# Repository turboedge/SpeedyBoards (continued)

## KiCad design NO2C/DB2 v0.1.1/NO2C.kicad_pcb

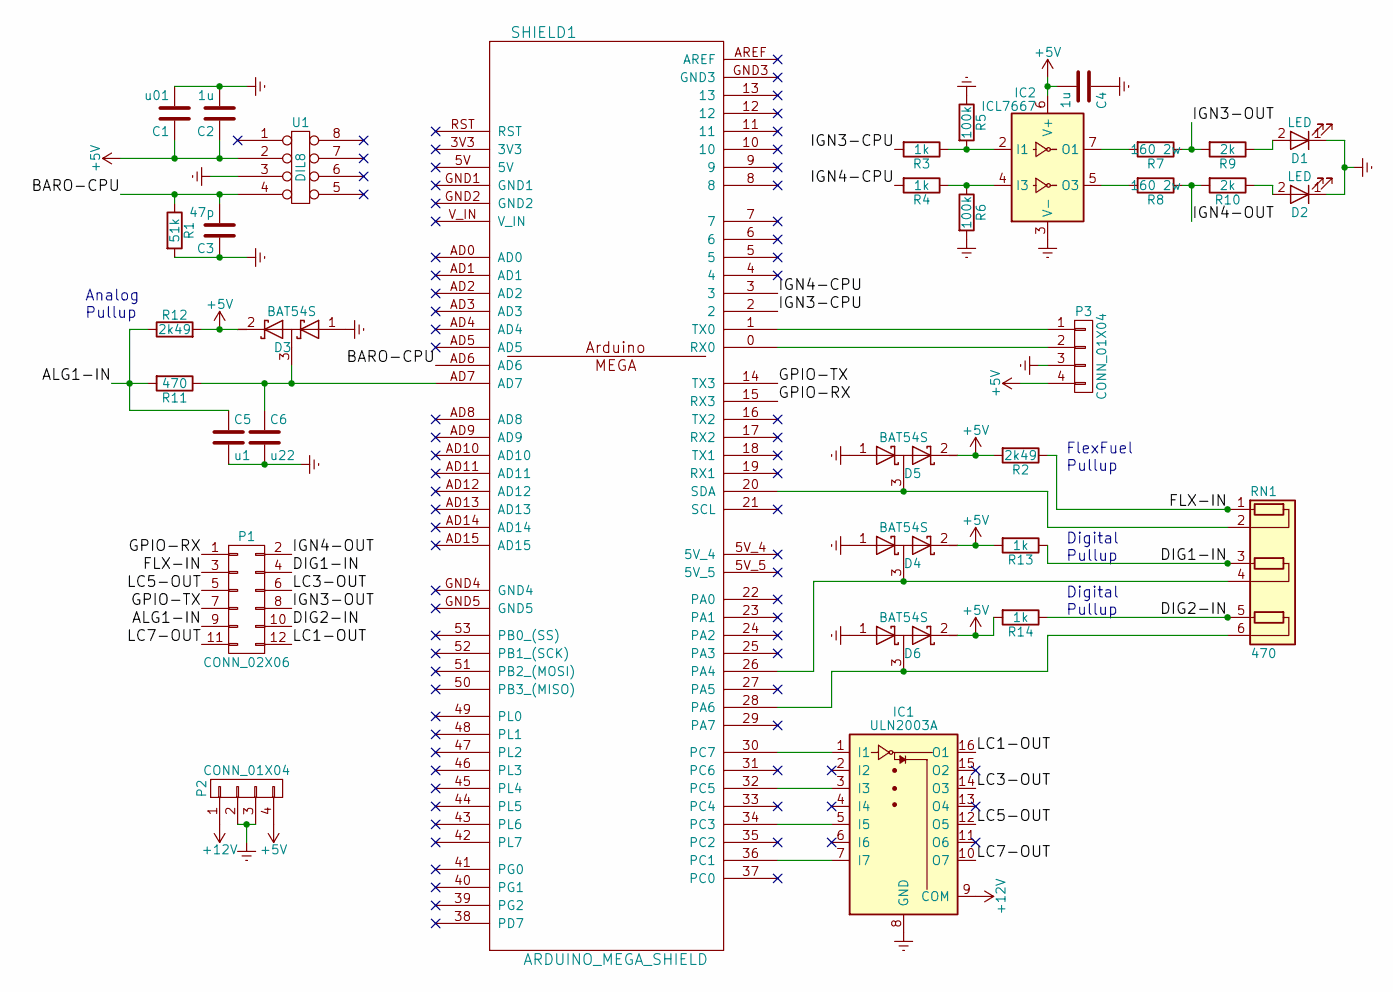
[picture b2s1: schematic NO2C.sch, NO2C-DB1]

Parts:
C1: u01; C_Disc_D3.8mm_W2.6mm_P2.50mm
C2, C4: 1u; C_Disc_D5.1mm_W3.2mm_P5.00mm
C3: 47p; C_1206_HandSoldering
C5: u1; C_Disc_D3.8mm_W2.6mm_P2.50mm
C6: u22; C_Disc_D3.8mm_W2.6mm_P2.50mm
D1, D2: LED; LED_D3.0mm
D3, D4, D5, D6: BAT54S; SOT-23_Handsoldering
IC1: ULN2003A; SOIC-16_3.9x9.9mm_Pitch1.27mm
IC2: ICL7667; DIP-8_W7.62mm
P1: CONN_02X06; Molex_Microfit3_Header_02x06_Straight_43045-1228
P2, P3: CONN_01X04; Pin_Header_Straight_1x04_Pitch2.54mm
R1: 51k; R_1206_HandSoldering
R2, R12: 2k49; R_Axial_DIN0207_L6.3mm_D2.5mm_P7.62mm_Horizontal
R3, R4: 1k; R_Axial_DIN0207_L6.3mm_D2.5mm_P7.62mm_Horizontal
R5, R6: 100k; R_Axial_DIN0204_L3.6mm_D1.6mm_P7.62mm_Horizontal
R7, R8: 160 2w; R_Axial_DIN0411_L9.9mm_D3.6mm_P12.70mm_Horizontal
R9, R10: 2k; R_Axial_DIN0207_L6.3mm_D2.5mm_P7.62mm_Horizontal
R11: 470; R_Axial_DIN0207_L6.3mm_D2.5mm_P7.62mm_Horizontal
R13, R14: 1k; R_1206
RN1: 470; R_Array_SIP6
SHIELD1: ARDUINO_MEGA_SHIELD; ARDUINO_MEGA_SHIELD_DB
U1: DIL8; SSO-8_9.6x6.3mm_Pitch1.27mm_Clearance10.5mm

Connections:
+5V: C1.1, C2.1, C4.2, D3.2 (K), D4.2 (K), D5.2 (K), D6.2 (K), IC2.6 (V+), P2.4, P3.4, R2.2, R12.2, R13.2, R14.2, U1.2
+12V: IC1.9 (COM), P2.1
/ALG1-IN: C5.1, P1.9, R11.2, R12.1
/BARO-CPU: C3.2, R1.1, SHIELD1.AD6, U1.4
/DIG1-IN: P1.4, R13.1, RN1.3 (R2.1)
/DIG2-IN: P1.10, R14.1, RN1.5 (R3.1)
/FLX-IN: P1.3, R2.1, RN1.1 (R1.1)
/GPIO-RX: P1.1, SHIELD1.15 (RX3)
/GPIO-TX: P1.7, SHIELD1.14 (TX3)
/IGN3-CPU: R3.2, SHIELD1.2
/IGN3-OUT: P1.8, R7.1, R9.2
/IGN4-CPU: R4.2, SHIELD1.3
/IGN4-OUT: P1.2, R8.1, R10.2
/LC1-OUT: IC1.16 (O1), P1.12
/LC3-OUT: IC1.14 (O3), P1.6
/LC5-OUT: IC1.12 (O5), P1.5
/LC7-OUT: IC1.10 (O7), P1.11
Earth: C1.2, C2.2, C3.1, C4.1, C5.2, C6.2, D1.1 (K), D2.1 (K), D3.1 (A), D4.1 (A), D5.1 (A), D6.1 (A), IC1.8 (GND), IC2.3 (V-), P2.2, P2.3, P3.3, R1.2, R5.1, R6.2, U1.3
unnamed: C6.1, D3.3 (common), R11.1, SHIELD1.AD7
unnamed: D1.2 (A), R9.1
unnamed: D2.2 (A), R10.1
unnamed: D4.3 (common), RN1.4 (R2.2), SHIELD1.26 (PA4)
unnamed: D5.3 (common), RN1.2 (R1.2), SHIELD1.20 (SDA)
unnamed: D6.3 (common), RN1.6 (R3.2), SHIELD1.28 (PA6)
unnamed: IC1.1 (I1), SHIELD1.30 (PC7)
unnamed: IC1.3 (I3), SHIELD1.32 (PC5)
unnamed: IC1.5 (I5), SHIELD1.34 (PC3)
unnamed: IC1.7 (I7), SHIELD1.36 (PC1)
unnamed: IC2.2 (I1), R3.1, R5.2
unnamed: IC2.4 (I3), R4.1, R6.1
unnamed: IC2.5 (O3), R8.2
unnamed: IC2.7 (O1), R7.2
unnamed: P3.1, SHIELD1.1 (TX0)
unnamed: P3.2, SHIELD1.0 (RX0)

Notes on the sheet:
FlexFuel Pullup
Digital Pullup
Analog Pullup

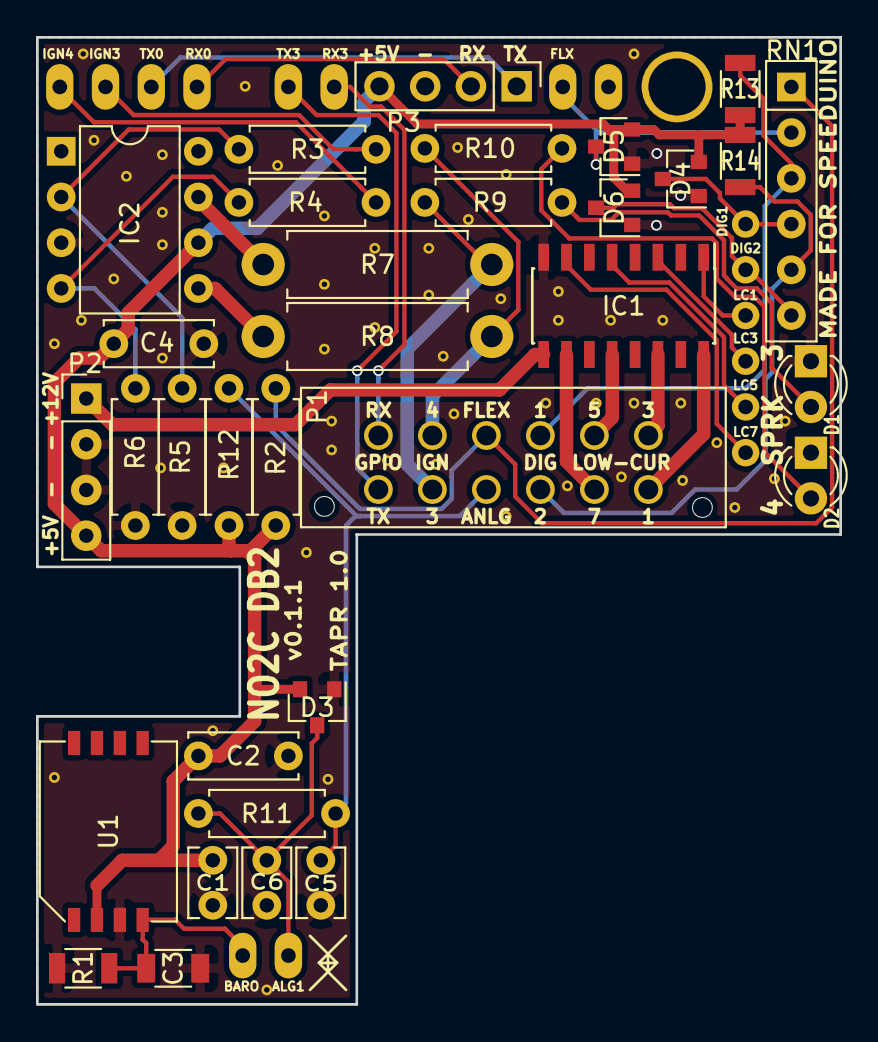
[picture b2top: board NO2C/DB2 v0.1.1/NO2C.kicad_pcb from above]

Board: 2 copper layers, 44.6 x 53.7 mm, 34 parts (0 on the bottom side), 34 nets.

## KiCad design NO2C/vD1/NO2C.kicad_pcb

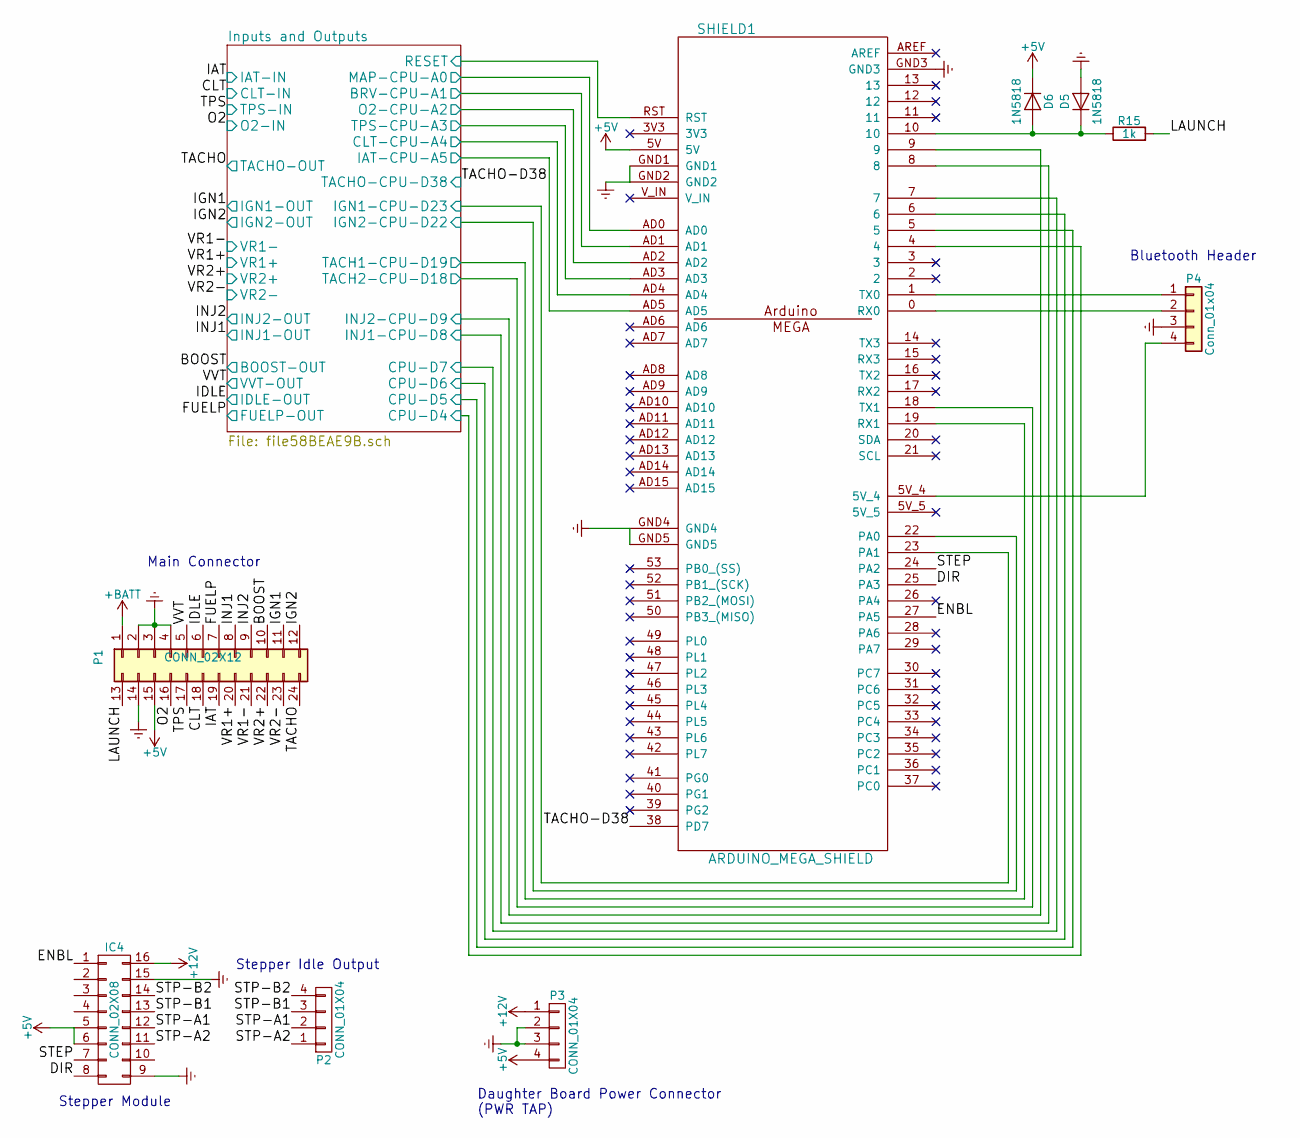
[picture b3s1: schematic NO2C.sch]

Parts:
D5, D6: 1N5818; D_DO-41_SOD81_P7.62mm_Horizontal
IC4: CONN_02X08; DRV8825
P1: CONN_02X12; Molex_Microfit3_Header_02x12_Straight_43045-2428
P2: CONN_01X04; Molex_Microfit3_Header_02x02_Angled_43045-040x
P3: CONN_01X04; Pin_Header_Straight_1x04_Pitch2.54mm
P4: Conn_01x04; Socket_Strip_Straight_1x04_Pitch2.54mm
R15: 1k; R_Axial_DIN0207_L6.3mm_D2.5mm_P7.62mm_Horizontal
SHIELD1: ARDUINO_MEGA_SHIELD

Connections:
+5V: D6.1 (K), IC4.5, IC4.6, P1.15, P3.4, SHIELD1.5V; also elsewhere on the board
+12V: IC4.16, P1.1, P3.1; also elsewhere on the board
/BOOST: P1.10; also elsewhere on the board
/CLT: P1.18; also elsewhere on the board
/DIR: IC4.8, SHIELD1.25 (PA3)
/ENBL: IC4.1, SHIELD1.27 (PA5)
/FUELP: P1.7; also elsewhere on the board
/IAT: P1.19; also elsewhere on the board
/IDLE: P1.6; also elsewhere on the board
/IGN1: P1.11; also elsewhere on the board
/IGN2: P1.12; also elsewhere on the board
/INJ1: P1.8; also elsewhere on the board
/INJ2: P1.9; also elsewhere on the board
/Inputs and Outputs/BRV-CPU-A1: SHIELD1.AD1; also elsewhere on the board
/Inputs and Outputs/CLT-CPU-A4: SHIELD1.AD4; also elsewhere on the board
/Inputs and Outputs/CPU-D4: SHIELD1.4; also elsewhere on the board
/Inputs and Outputs/CPU-D5: SHIELD1.5; also elsewhere on the board
/Inputs and Outputs/CPU-D6: SHIELD1.6; also elsewhere on the board
/Inputs and Outputs/CPU-D7: SHIELD1.7; also elsewhere on the board
/Inputs and Outputs/IAT-CPU-A5: SHIELD1.AD5; also elsewhere on the board
/Inputs and Outputs/IGN1-CPU-D23: SHIELD1.23 (PA1); also elsewhere on the board
/Inputs and Outputs/IGN2-CPU-D22: SHIELD1.22 (PA0); also elsewhere on the board
/Inputs and Outputs/INJ1-CPU-D8: SHIELD1.8; also elsewhere on the board
/Inputs and Outputs/INJ2-CPU-D9: SHIELD1.9; also elsewhere on the board
/Inputs and Outputs/MAP-CPU-A0: SHIELD1.AD0; also elsewhere on the board
/Inputs and Outputs/O2-CPU-A2: SHIELD1.AD2; also elsewhere on the board
/Inputs and Outputs/RESET: SHIELD1.RST; also elsewhere on the board
/Inputs and Outputs/TACH1-CPU-D19: SHIELD1.19 (RX1); also elsewhere on the board
/Inputs and Outputs/TACH2-CPU-D18: SHIELD1.18 (TX1); also elsewhere on the board
/Inputs and Outputs/TPS-CPU-A3: SHIELD1.AD3; also elsewhere on the board
/LAUNCH: P1.13, R15.2
/O2: P1.16; also elsewhere on the board
/STEP: IC4.7, SHIELD1.24 (PA2)
/STP-A1: IC4.12, P2.2
/STP-A2: IC4.11, P2.1
/STP-B1: IC4.13, P2.3
/STP-B2: IC4.14, P2.4
/TACHO: P1.24; also elsewhere on the board
/TACHO-D38: SHIELD1.38 (PD7); also elsewhere on the board
/TPS: P1.17; also elsewhere on the board
/VR1+: P1.20; also elsewhere on the board
/VR1-: P1.21; also elsewhere on the board
/VR2+: P1.22; also elsewhere on the board
/VR2-: P1.23; also elsewhere on the board
/VVT: P1.5; also elsewhere on the board
Earth: D5.2 (A), IC4.9, IC4.15, P1.2, P1.3, P1.4, P1.14, P3.2, P3.3, P4.3, SHIELD1.GND1, SHIELD1.GND2, SHIELD1.GND3, SHIELD1.GND4, SHIELD1.GND5; also elsewhere on the board
unnamed: D5.1 (K), D6.2 (A), R15.1, SHIELD1.10
unnamed: P4.1, SHIELD1.1 (TX0)
unnamed: P4.2, SHIELD1.0 (RX0)
unnamed: P4.4, SHIELD1.5V_4

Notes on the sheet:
Stepper Module
Daughter Board Power Connector (PWR TAP)
Bluetooth Header
Stepper Idle Output
Main Connector

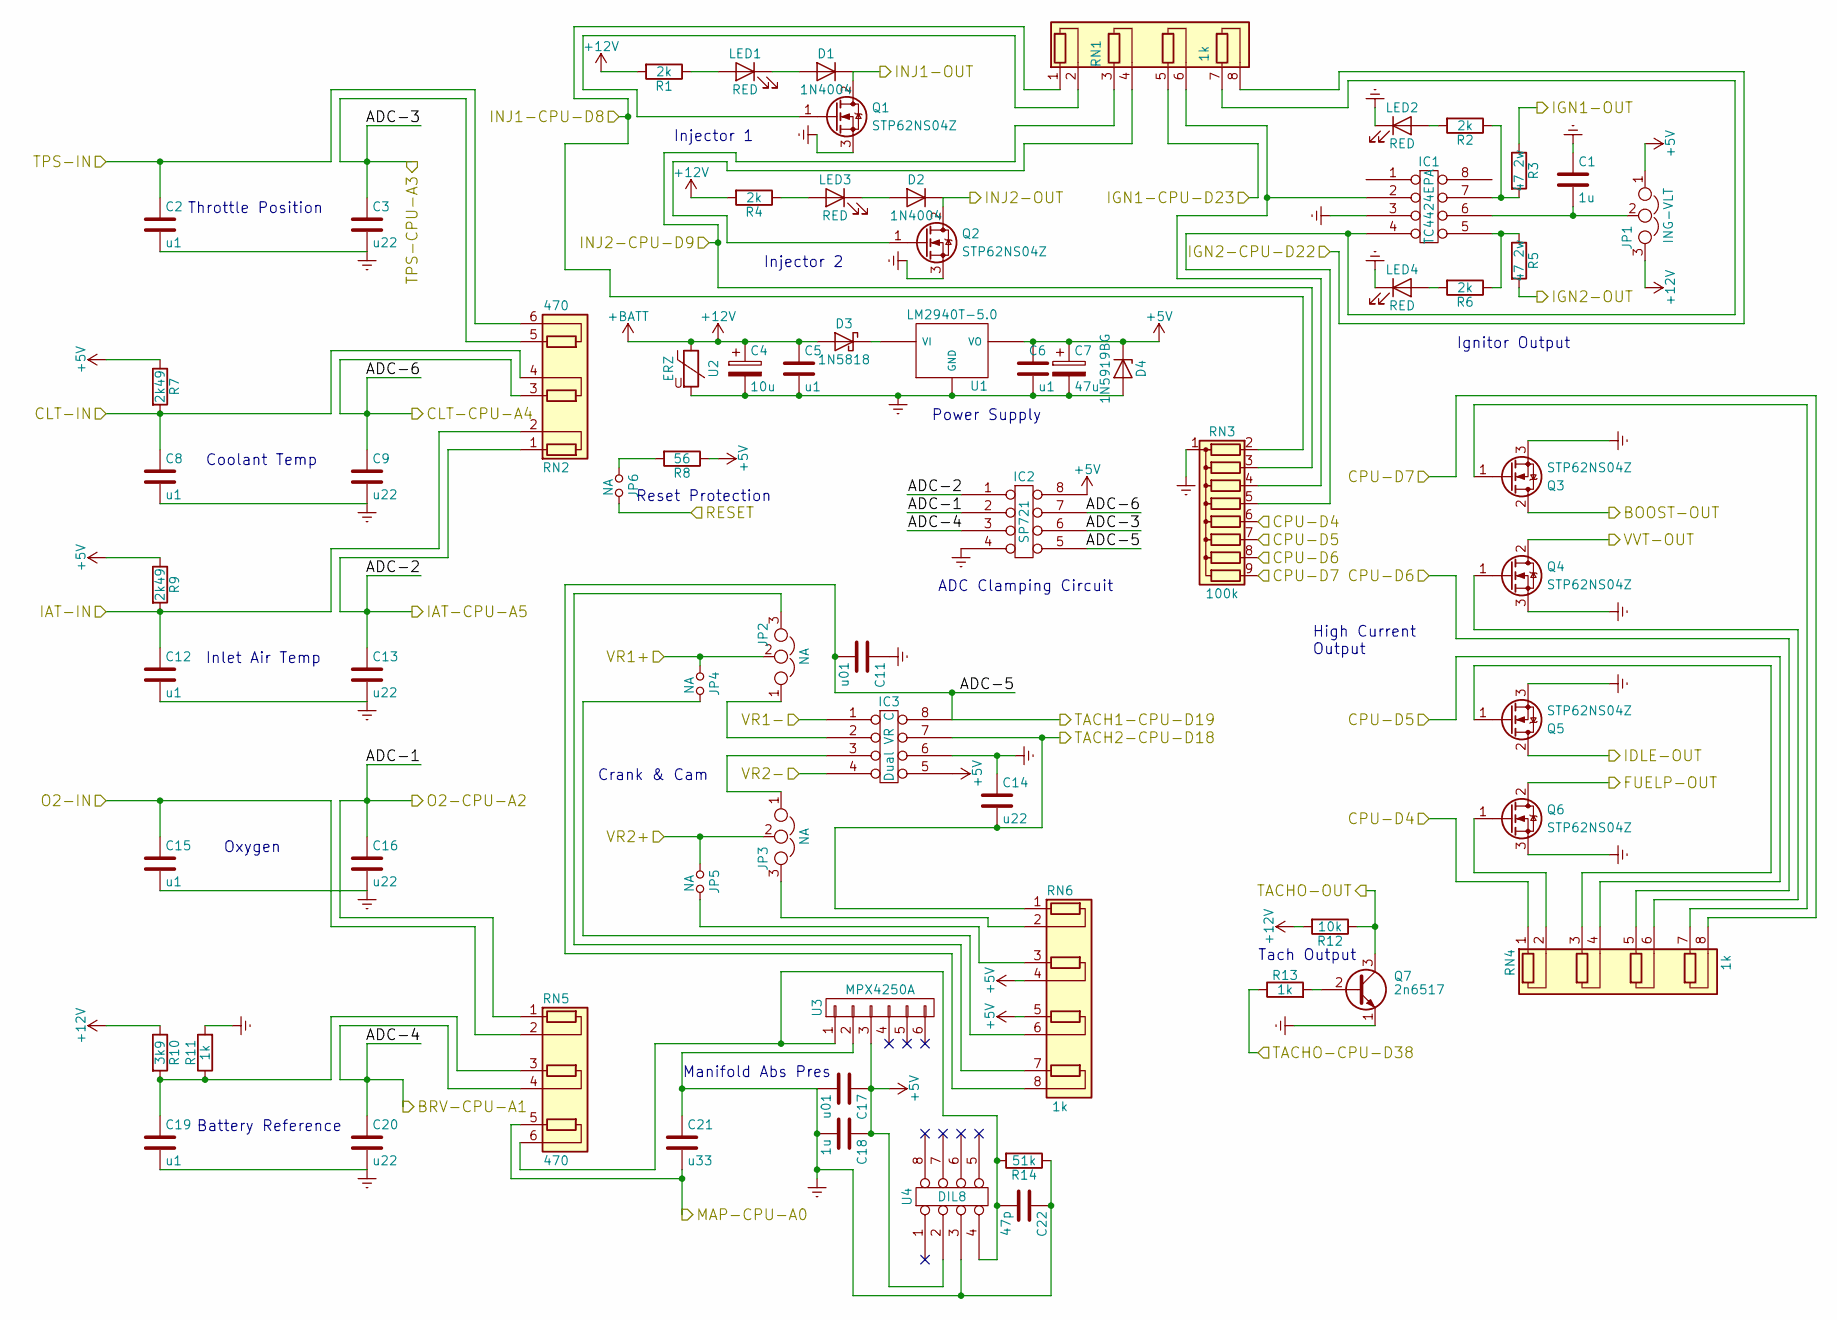
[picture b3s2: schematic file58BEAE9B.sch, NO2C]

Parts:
C1, C18: 1u; C_Disc_D6.0mm_W2.5mm_P5.00mm
C2, C5, C6, C8, C12, C15, C19: u1; C_Disc_D3.8mm_W2.6mm_P2.50mm
C3, C9, C13, C14, C16, C20: u22; C_Disc_D3.8mm_W2.6mm_P2.50mm
C4: 10u; CP_Radial_Tantal_D6.0mm_P2.50mm
C7: 47u; CP_Radial_Tantal_D6.0mm_P2.50mm
C11, C17: u01; C_Disc_D3.8mm_W2.6mm_P2.50mm
C21: u33; C_Disc_D3.8mm_W2.6mm_P2.50mm
C22: 47p; C_1206
D1, D2: 1N4004; D_DO-41_SOD81_P7.62mm_Horizontal
D3: 1N5818; D_DO-41_SOD81_P7.62mm_Horizontal
D4: 1N5919BG; D_DO-41_SOD81_P7.62mm_Horizontal
IC1: TC4424EPA; DIP-8_W7.62mm
IC2: SP721; DIP-8_W7.62mm
IC3: Dual VR C; DIP-8_W7.62mm_Socket
JP1: ING-VLT; Pin_Header_Straight_1x03_Pitch2.54mm
JP2, JP3: NA; Pin_Header_Straight_1x03_Pitch2.54mm
JP4, JP5, JP6: NA; Pin_Header_Straight_1x02_Pitch2.54mm
LED1, LED2, LED3, LED4: RED; LED_D3.0mm
Q1, Q2, Q3, Q4, Q5, Q6: STP62NS04Z; TO-220_Vertical
Q7: 2n6517; TO-92_Molded_Narrow
R1, R2, R4, R6: 2k; R_Axial_DIN0207_L6.3mm_D2.5mm_P7.62mm_Horizontal
R3, R5: 47 2w; R_Axial_DIN0411_L9.9mm_D3.6mm_P12.70mm_Horizontal
R7, R9: 2k49; R_Axial_DIN0207_L6.3mm_D2.5mm_P7.62mm_Horizontal
R8: 56; R_Axial_DIN0207_L6.3mm_D2.5mm_P7.62mm_Horizontal
R10: 3k9; R_Axial_DIN0207_L6.3mm_D2.5mm_P7.62mm_Horizontal
R11, R13: 1k; R_Axial_DIN0207_L6.3mm_D2.5mm_P7.62mm_Horizontal
R12: 10k; R_Axial_DIN0207_L6.3mm_D2.5mm_P7.62mm_Horizontal
R14: 51k; R_1206
RN1, RN4, RN6: 1k; R_Array_SIP8
RN2, RN5: 470; R_Array_SIP6
RN3: 100k; R_Array_SIP9
U1: LM2940T-5.0; TO-220_Vertical
U2: ERZ; RV_Disc_D15.5_W4.2_P7.5
U3: MPX4250A
U4: DIL8; NXP_Pressure_Sensor_SSOP

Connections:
+5V: C6.1, C7.1, C17.1, C18.1, D4.1 (K), IC2.8, IC3.5, JP1.1, R7.1, R8.1, R9.1, RN6.4 (R2.2), RN6.5 (R3.1), U1.3 (VO), U3.3, U4.2; also elsewhere on the board
+12V: C4.1, C5.1, D3.2 (A), JP1.3, R1.2, R4.2, R10.1, R12.2, U2.1; also elsewhere on the board
/BOOST: Q3.2 (D); also elsewhere on the board
/CLT: C8.1, R7.2, RN2.4 (R2.2); also elsewhere on the board
/FUELP: Q6.2 (D); also elsewhere on the board
/IAT: C12.1, R9.2, RN2.2 (R1.2); also elsewhere on the board
/IDLE: Q5.2 (D); also elsewhere on the board
/IGN1: R3.1; also elsewhere on the board
/IGN2: R5.2; also elsewhere on the board
/INJ1: D1.1 (K), Q1.2 (D); also elsewhere on the board
/INJ2: D2.1 (K), Q2.2 (D); also elsewhere on the board
/Inputs and Outputs/BRV-CPU-A1: C20.1, IC2.3, RN5.4 (R2.2); also elsewhere on the board
/Inputs and Outputs/CLT-CPU-A4: C9.1, IC2.7, RN2.3 (R2.1); also elsewhere on the board
/Inputs and Outputs/CPU-D4: RN3.6 (R5), RN4.1 (R1.1); also elsewhere on the board
/Inputs and Outputs/CPU-D5: RN3.7 (R6), RN4.4 (R2.2); also elsewhere on the board
/Inputs and Outputs/CPU-D6: RN3.8 (R7), RN4.5 (R3.1); also elsewhere on the board
/Inputs and Outputs/CPU-D7: RN3.9 (R8), RN4.8 (R4.2); also elsewhere on the board
/Inputs and Outputs/IAT-CPU-A5: C13.1, IC2.1, RN2.1 (R1.1); also elsewhere on the board
/Inputs and Outputs/IGN1-CPU-D23: RN1.5 (R3.1); also elsewhere on the board
/Inputs and Outputs/IGN2-CPU-D22: RN1.8 (R4.2); also elsewhere on the board
/Inputs and Outputs/INJ1-CPU-D8: RN1.1 (R1.1), RN3.2 (R1); also elsewhere on the board
/Inputs and Outputs/INJ2-CPU-D9: RN1.3 (R2.1), RN3.3 (R2); also elsewhere on the board
/Inputs and Outputs/MAP-CPU-A0: C21.2, RN5.5 (R3.1); also elsewhere on the board
/Inputs and Outputs/O2-CPU-A2: C16.1, IC2.2, RN5.1 (R1.1); also elsewhere on the board
/Inputs and Outputs/RESET: JP6.2; also elsewhere on the board
/Inputs and Outputs/TACH1-CPU-D19: C11.2, IC2.5, IC3.8, RN6.8 (R4.2); also elsewhere on the board
/Inputs and Outputs/TACH2-CPU-D18: C14.2, IC3.7, RN6.1 (R1.1); also elsewhere on the board
/Inputs and Outputs/TPS-CPU-A3: C3.1, IC2.6, RN2.5 (R3.1); also elsewhere on the board
/O2: C15.1, RN5.2 (R1.2); also elsewhere on the board
/TACHO: Q7.3 (C), R12.1; also elsewhere on the board
/TACHO-D38: R13.1; also elsewhere on the board
/TPS: C2.1, RN2.6 (R3.2); also elsewhere on the board
/VR1+: JP2.2, JP4.1; also elsewhere on the board
/VR1-: IC3.1; also elsewhere on the board
/VR2+: JP3.2, JP5.1; also elsewhere on the board
/VR2-: IC3.4; also elsewhere on the board
/VVT: Q4.2 (D); also elsewhere on the board
Earth: C1.1, C2.2, C3.2, C4.2, C5.2, C6.2, C7.2, C8.2, C9.2, C11.1, C12.2, C13.2, C14.1, C15.2, C16.2, C17.2, C18.2, C19.2, C20.2, C21.1, C22.1, D4.2 (A), IC1.3, IC2.4, IC3.6, LED2.1 (K), LED4.1 (K), Q1.3 (S), Q2.3 (S), Q3.3 (S), Q4.3 (S), Q5.3 (S), Q6.3 (S), Q7.1 (E), R11.2, R14.1, RN3.1 (common), U1.2 (GND), U2.2, U3.2, U4.3; also elsewhere on the board
unnamed: C1.2, IC1.6, JP1.2
unnamed: C19.1, R10.2, R11.1, RN5.3 (R2.1)
unnamed: C22.2, R14.2, RN5.6 (R3.2), U3.1, U4.4
unnamed: D1.2 (A), LED1.1 (K)
unnamed: D2.2 (A), LED3.1 (K)
unnamed: D3.1 (K), U1.1 (VI)
unnamed: IC1.2, RN1.6 (R3.2), RN3.4 (R3)
unnamed: IC1.4, RN1.7 (R4.1), RN3.5 (R4)
unnamed: IC1.5, R5.1, R6.1
unnamed: IC1.7, R2.1, R3.2
unnamed: IC3.2, JP2.1
unnamed: IC3.3, JP3.1
unnamed: JP2.3, RN6.7 (R4.1)
unnamed: JP3.3, RN6.2 (R1.2)
unnamed: JP4.2, RN6.6 (R3.2)
unnamed: JP5.2, RN6.3 (R2.1)
unnamed: JP6.1, R8.2
unnamed: LED1.2 (A), R1.1
unnamed: LED2.2 (A), R2.2
unnamed: LED3.2 (A), R4.1
unnamed: LED4.2 (A), R6.2
unnamed: Q1.1 (G), RN1.2 (R1.2)
unnamed: Q2.1 (G), RN1.4 (R2.2)
unnamed: Q3.1 (G), RN4.7 (R4.1)
unnamed: Q4.1 (G), RN4.6 (R3.2)
unnamed: Q5.1 (G), RN4.3 (R2.1)
unnamed: Q6.1 (G), RN4.2 (R1.2)
unnamed: Q7.2 (B), R13.2

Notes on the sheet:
Throttle Position
Inlet Air Temp
Coolant Temp
Oxygen
Battery Reference
Manifold Abs Pres
Crank & Cam
ADC Clamping Circuit
Reset Protection
Power Supply
Injector 1
Injector 2
Ignitor Output
Tach Output
High Current Output

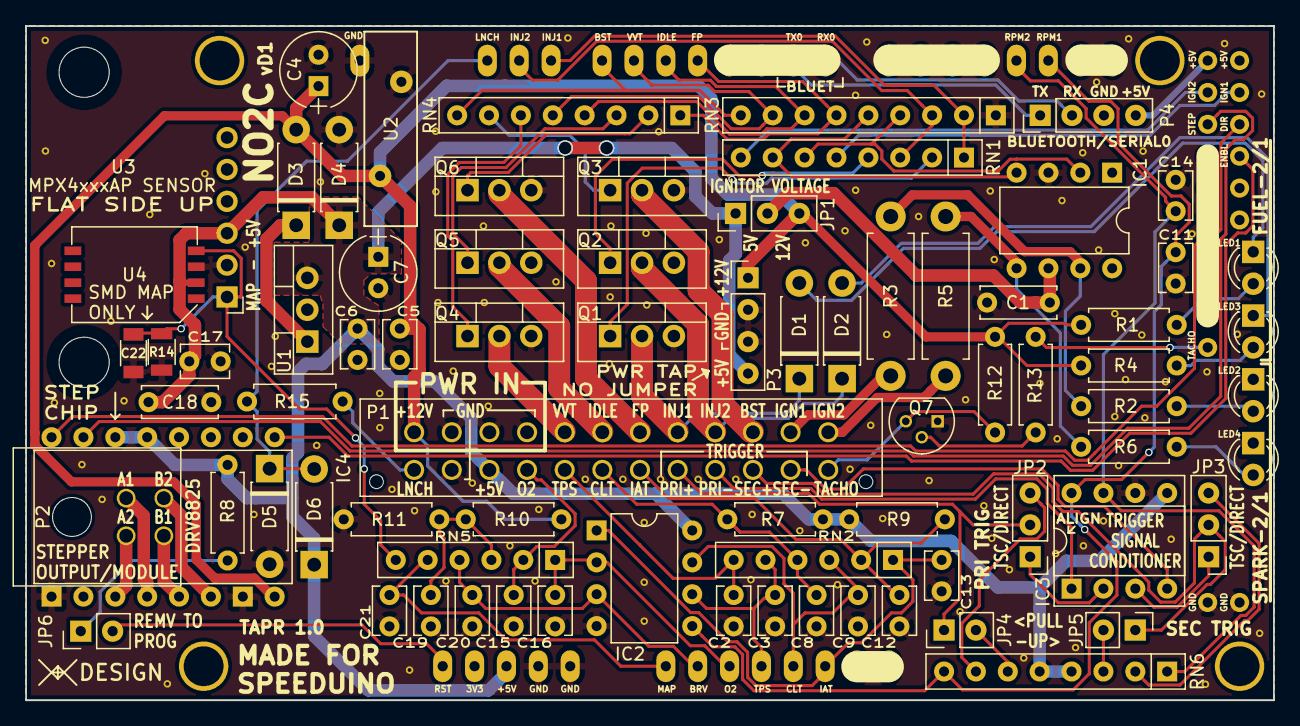
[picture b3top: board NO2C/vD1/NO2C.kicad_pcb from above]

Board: 2 copper layers, 99.4 x 53.7 mm, 78 parts (0 on the bottom side), 78 nets.

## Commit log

2017-10-20 Add files via upload
    Added NO2C v0.2.0 files
2017-10-20 Add files via upload
    Added NO2C v0.1.1 files
2017-11-04 BOM and Code Changes
    Removed CODE folder as the latest version is now in main Speeduino project. Updated v0.1.1 BOM.
2017-11-18 Updated BOM
    Added more connector information.
2017-11-18 BOM Changes
    Add high voltage tacho transistor option.
2017-11-22 More BOM info
2017-12-31 BOM Tweeks Schema Add
2018-01-23 Corrected jumper numbers in BOM
2018-02-02 Update BOM, Arrange folders for future versions
2018-03-18 Upload of NO2C v0.2.1
2018-06-03 NO2C v.0.2.2
2018-07-22 Corrected NO2C 0.2.2 Renders
2018-08-05 Added NO2C Case STL
2018-11-20 UA4C vA3
    Upload Seawolf Documents
2018-12-17 Added UA4C vA3 Schematics
2018-12-17 Added UA4C vA3 Design Files
2019-08-24 New UA4C and NO2C revisions
    Added new board revisions and organized files
2019-08-27 Correct UA4C vB1 files
    Layout, schematics and renders were from old version
2019-11-17 Add Connector Application Guide
    Added Minitek PWR 3.0 Application information with details about how the 3mm connections are assembled, both standard and high-current.
2020-06-20 Added UA4CvB2 and NO2CvD1 information
2020-10-13 Add DB2
2022-03-21 Add new UA4C revisions
    B3, C2, C3
2022-03-21 Updated board layout files
2024-01-24 UA4C C4 C5
    New revision upload
2024-07-15 Load Ocelot schem and render
2024-08-09 Update README.md
    Correct Spelling
2024-09-20 Updated connector map file
    Fixed pin connector pin number and added some color
2024-09-23 Update README.md
    Add Errata for Ocelot trigger jumpers
2024-09-23 Update README.md
    Spelling correction
2024-10-10 Update README.md
    Tweaked firmware loading instructions for Ocelot
2024-10-10 Update README.md
    updated UA4C version number
2024-10-25 Updated Ocelot connector sheet
    Slightly changed colors to match future pigtails and added some quick tips.
2024-11-08 Update README.md
    Update Ocelot information
